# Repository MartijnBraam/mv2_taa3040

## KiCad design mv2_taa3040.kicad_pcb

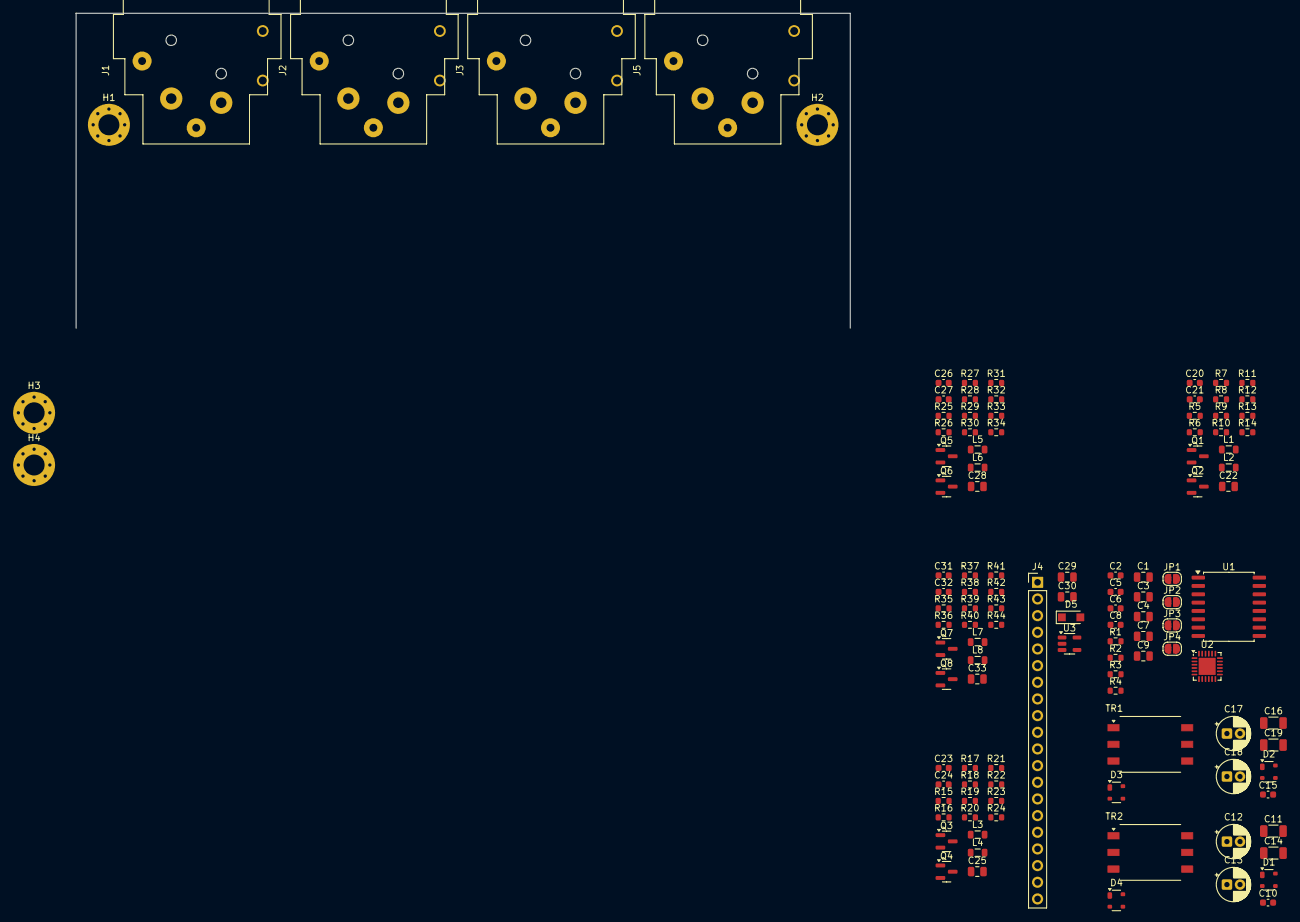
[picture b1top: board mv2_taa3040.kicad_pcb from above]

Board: 4 copper layers, 116 parts (0 on the bottom side), 69 nets, no tracks yet.

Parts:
C1, C9, C22, C25, C28, C33: 10μF; C_0805_2012Metric
C2, C5, C6, C8: 100nF; C_0603_1608Metric
C3, C4, C7, C29, C30: 1μF; C_0805_2012Metric
C10, C15: 2.2nF 63V; C_0603_1608Metric
C11, C14, C16, C19: 2.2μF 100V; C_1206_3216Metric
C12, C13, C17, C18: 10μF 100V; CP_Radial_D5.0mm_P2.00mm
C20, C21, C23, C24, C26, C27, C31, C32: 1nF 63V; C_0603_1608Metric
D1, D2, D3, D4: PRTR5V0U2X; SOT-143
D5: PTVS5V0S1UR,115; Nexperia_CFP3_SOD-123W
H1, H2, H3, H4: MountingHole_Pad; MountingHole_3.2mm_M3_Pad_Via
J1, J2, J3, J5: NC3FAH1; Jack_XLR_Neutrik_NC3FAH2-LR-DAE_Horizontal
J4: Interconnect; PinHeader_1x20_P2.54mm_Vertical
JP1, JP2, JP3, JP4: Jumper_2_Small_Bridged; SolderJumper-2_P1.3mm_Open_RoundedPad1.0x1.5mm
L1, L2, L3, L4, L5, L6, L7, L8: 10μH 15mA; L_0805_2012Metric
Q1, Q3, Q5, Q7: 2N7002; SOT-23
Q2, Q4, Q6, Q8: SI2309CDS-T1-GE3; SOT-23
R1, R2, R3, R4, R7, R11, R17, R21, R27, R31, R37, R41: 100kΩ; R_0603_1608Metric
R5, R15, R25, R35: 10kΩ; R_0603_1608Metric
R6, R16, R26, R36: 22kΩ; R_0603_1608Metric
R8, R10, R18, R20, R28, R30, R38, R40: 6.8kΩ; R_0603_1608Metric
R9, R19, R29, R39: 470Ω; R_0603_1608Metric
R12, R13, R22, R23, R32, R33, R42, R43: 2.2kΩ; R_0603_1608Metric
R14, R24, R34, R44: 13kΩ; R_0603_1608Metric
TR1, TR2: 750315371; Transformer_Wuerth_750315371
U1: TCA9534; SOIC-16W_7.5x10.3mm_P1.27mm
U2: TAA3040; WQFN-24-1EP_4x4mm_P0.5mm_EP2.6x2.6mm
U3: LP5907MFX-3.3; SOT-23-5

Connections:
+3.3V: C6.1, C7.1, J4.2 (+3V3), JP1.2 (B), JP2.2 (B), JP3.2 (B), JP4.2 (B), U1.16 (VDD), U2.19 (IOVDD)
+3.3VA: C3.1, C5.1, C30.1, D1.4 (VCC), D2.4 (VCC), D3.4 (VCC), D4.4 (VCC), D5.1 (K), U2.1 (AVDD), U3.5 (OUT)
+5VA: C29.1, J4.6 (+5VA), U3.1 (IN), U3.3 (EN)
+48V: J4.1 (+48V), Q2.3 (D), Q4.3 (D), Q6.3 (D), Q8.3 (D), R6.1, R16.1, R26.1, R36.1
/Balanced Input 1/COLD: C13.2, C14.2, D1.3 (I/O2), U2.7 (IN1-)
/Balanced Input 1/HOT: C11.2, C12.2, D1.2 (I/O1), U2.6 (IN1+)
/Balanced Input 1/Input frontend/COLD: C10.1, C13.1, C14.1, R43.2, R44.2
/Balanced Input 1/Input frontend/HOT: C10.2, C11.1, C12.1, R42.2, R44.1
/Balanced Input 1/PHANTOM: Q7.1 (G), R35.1, U1.4 (P0)
/Balanced Input 2/COLD: C18.2, C19.2, D2.3 (I/O2), U2.9 (IN2-)
/Balanced Input 2/HOT: C16.2, C17.2, D2.2 (I/O1), U2.8 (IN2+)
/Balanced Input 2/Input frontend/COLD: C15.1, C18.1, C19.1, R23.2, R24.2
/Balanced Input 2/Input frontend/HOT: C15.2, C16.1, C17.1, R22.2, R24.1
/Balanced Input 2/PHANTOM: Q3.1 (G), R15.1, U1.5 (P1)
/Balanced Input 3/COLD: D4.3 (I/O2), TR2.4, U2.11 (IN3-)
/Balanced Input 3/HOT: D4.2 (I/O1), TR2.6, U2.10 (IN3+)
/Balanced Input 3/Input frontend/COLD: R13.2, R14.2, TR2.3
/Balanced Input 3/Input frontend/HOT: R12.2, R14.1, TR2.1
/Balanced Input 3/PHANTOM: Q1.1 (G), R5.1, U1.6 (P2)
/Balanced Input 4/COLD: D3.3 (I/O2), TR1.4, U2.13 (IN4-)
/Balanced Input 4/HOT: D3.2 (I/O1), TR1.6, U2.12 (IN4+)
/Balanced Input 4/Input frontend/COLD: R33.2, R34.2, TR1.3
/Balanced Input 4/Input frontend/HOT: R32.2, R34.1, TR1.1
/Balanced Input 4/PHANTOM: Q5.1 (G), R25.1, U1.7 (P3)
/Conn and power/I2S_BCLK: J4.11 (I2S1_BCLK), U2.22 (BCLK)
/Conn and power/I2S_MCLK: J4.10 (I2S1_MCLK), U2.23 (FSYNC)
/Conn and power/I2S_RX: J4.9 (I2S1_RX1), U2.21 (SDOUT)
/Conn and power/SCL: J4.14 (SCL), U1.14 (SCL), U2.17 (SCL)
/Conn and power/SDA: J4.15 (SDA), U1.15 (SDA), U2.18 (SDA)
GND: C1.2, C2.2, C3.2, C4.2, C5.2, C6.2, C7.2, C8.2, C9.2, C20.2, C21.1, C22.1, C23.2, C24.1, C25.1, C26.2, C27.1, C28.1, C29.2, C30.2, C31.2, C32.1, C33.1, D1.1 (GND), D2.1 (GND), D3.1 (GND), D4.1 (GND), D5.2 (A), H1.1, H2.1, H3.1, H4.1, J1.1, J1.G, J2.1, J2.G, J3.1, J3.G, J4.7 (GND), J4.13 (GND), J4.20 (GND), J5.1, J5.G, Q1.3 (D), Q3.3 (D), Q5.3 (D), Q7.3 (D), R1.2, R2.2, R3.2, R4.2, R5.2, R11.2, R15.2, R21.2, R25.2, R31.2, R35.2, R41.2, U1.2 (A1), U1.8 (GND), U2.4 (AVSS), U2.14 (~SHDNZ), U2.25 (VSS), U3.2 (GND)
unnamed: C20.1, J1.2, L2.1
unnamed: C21.2, J1.3, L1.1
unnamed: C22.2, R8.1, R9.2, R10.1, R11.1
unnamed: C23.1, J2.2, L4.1
unnamed: C24.2, J2.3, L3.1
unnamed: C25.2, R18.1, R19.2, R20.1, R21.1
unnamed: C26.1, J3.2, L6.1
unnamed: C27.2, J3.3, L5.1
unnamed: C28.2, R28.1, R29.2, R30.1, R31.1
unnamed: C31.1, J5.2, L8.1
unnamed: C32.2, J5.3, L7.1
unnamed: C33.2, R38.1, R39.2, R40.1, R41.1
unnamed: JP1.1 (A), R1.1, U1.1 (A0)
unnamed: JP2.1 (A), R2.1, U1.3 (A2)
unnamed: JP3.1 (A), R3.1, U2.15 (ADDR1)
unnamed: JP4.1 (A), R4.1, U2.16 (ADDR0)
unnamed: L1.2, R10.2, R13.1
unnamed: L2.2, R8.2, R12.1
unnamed: L3.2, R20.2, R23.1
unnamed: L4.2, R18.2, R22.1
unnamed: L5.2, R30.2, R33.1
unnamed: L6.2, R28.2, R32.1
unnamed: L7.2, R40.2, R43.1
unnamed: L8.2, R38.2, R42.1
unnamed: Q1.2 (S), R7.2
unnamed: Q2.1 (G), R6.2, R7.1
unnamed: Q2.2 (S), R9.1
unnamed: Q3.2 (S), R17.2
unnamed: Q4.1 (G), R16.2, R17.1
unnamed: Q4.2 (S), R19.1
unnamed: Q5.2 (S), R27.2
unnamed: Q6.1 (G), R26.2, R27.1
unnamed: Q6.2 (S), R29.1
unnamed: Q7.2 (S), R37.2
unnamed: Q8.1 (G), R36.2, R37.1
unnamed: Q8.2 (S), R39.1
unnamed: C1.1, C2.1, U2.2 (AREG)
unnamed: C8.1, C9.1, U2.24 (DREG)
unnamed: C4.1, U2.3 (VREF)

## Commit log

2025-06-07 some suggested changes to the schematic:
    - common pull-down mosfet for phantom power switch
    - added board interconnect header
    - proposed buffer for VREF
    - cosmetic changes
    - address selection jumpers
2025-06-08 independent phantom control and removed transformer bias
2025-06-08 assign some component data
2025-06-09 tvs clamps
2025-06-09 some final touches
2025-06-09 update component assignments
2025-06-10 sync pcb
